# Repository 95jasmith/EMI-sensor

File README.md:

# EMI-sensor

This folder is for EMI conductivity meter being developed by Jonah Smith at Kansas State University for Dr. Stacey Kulesza in the Civil 
Engineering department.
All files are for the prototype and have only had limited testing.

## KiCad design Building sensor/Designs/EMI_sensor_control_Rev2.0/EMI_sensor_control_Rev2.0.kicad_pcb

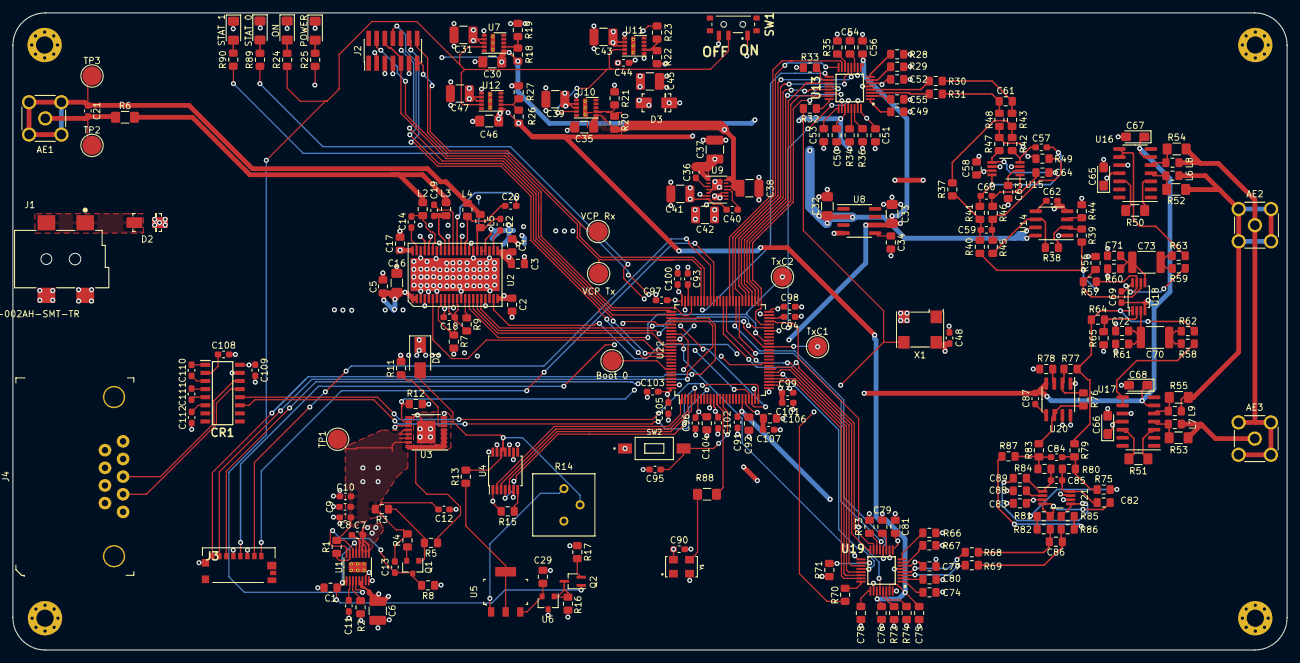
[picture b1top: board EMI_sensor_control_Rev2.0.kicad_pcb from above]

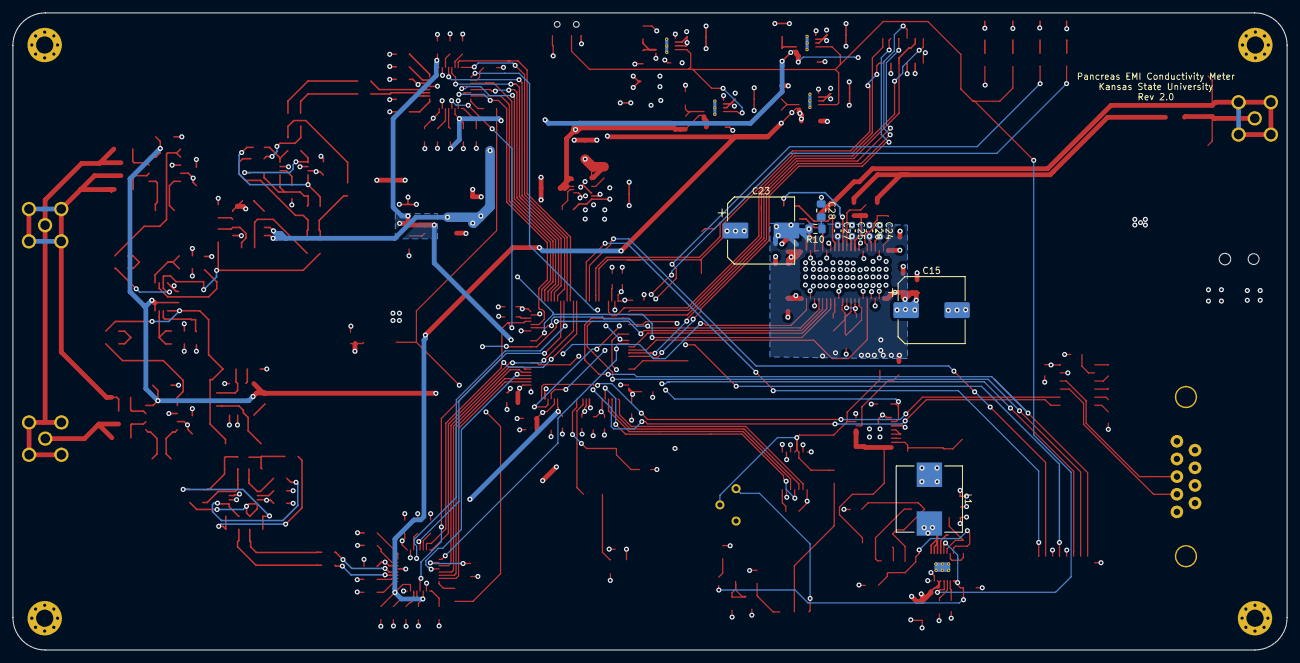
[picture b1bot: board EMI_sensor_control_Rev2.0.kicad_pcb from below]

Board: 4 copper layers, 200.0 x 100.0 mm, 266 parts (9 on the bottom side), 197 nets.

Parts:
AE1: Antenna_Loop Tx; SMA_Molex_73251-2200_Horizontal
AE2: Antenna_Loop Bx; SMA_Molex_73251-2200_Horizontal
AE3: Antenna_Loop Rx; SMA_Molex_73251-2200_Horizontal
Boot 0: TestPoint; TestPoint_Pad_D3.0mm
C1, C2, C3, C4, C5, C17, C29, C34, C49, C50, C51, C52, C53, C54, C55, C56, C58, C63, C74, C75, C76, C77, C78, C79, C80, C81, C83, C88, C92, C106: C 1u; C_0805_2012Metric_Pad1.15x1.40mm_HandSolder
C6, C31, C37, C38, C39, C41, C42, C43, C45, C47: C 10u; C_1210_3225Metric_Pad1.42x2.65mm_HandSolder
C7, C8, C9, C10, C11, C12, C14, C18, C19, C20, C22, C24, C25, C26, C27, C36, C40, C44, C48, C69, C90, C91, C95, C96, C97, C98, C99, C100, C101, C102, C103, C105, C107, C108, C109, C110, C111, C112: C 100n; C_0603_1608Metric_Pad1.05x0.95mm_HandSolder
C13, C60, C85: C 1n; C_0603_1608Metric_Pad1.05x0.95mm_HandSolder
C15: C 330u; CP_Elec_10x10
C16, C46: C 47u; C_1206_3216Metric_Pad1.42x1.75mm_HandSolder
C21: C 2700p; C_0603_1608Metric_Pad1.05x0.95mm_HandSolder
C23: C 470u; CP_Elec_10x10
C28: C 10n; C_0805_2012Metric_Pad1.15x1.40mm_HandSolder
C30: C 33u; C_1206_3216Metric_Pad1.42x1.75mm_HandSolder
C32: C 1u; C_1206_3216Metric_Pad1.42x1.75mm_HandSolder
C33, C35: C 22u; C_1206_3216Metric_Pad1.42x1.75mm_HandSolder
C57: C 270p; C_0603_1608Metric_Pad1.05x0.95mm_HandSolder
C59, C84: C 470p; C_0603_1608Metric_Pad1.05x0.95mm_HandSolder
C61, C86: C 22n; C_0805_2012Metric_Pad1.15x1.40mm_HandSolder
C62, C87: C 10p; C_0603_1608Metric_Pad1.05x0.95mm_HandSolder
C64, C82, C89: C 270p; C_0805_2012Metric_Pad1.15x1.40mm_HandSolder
C65, C66, C67, C68: C 100n; CP_EIA-3216-18_Kemet-A_Pad1.58x1.35mm_HandSolder
C70, C73: C 100n; C_1812_4532Metric_Pad1.30x3.40mm_HandSolder
C71, C72: C .047u; C_0805_2012Metric_Pad1.15x1.40mm_HandSolder
C93, C94: C 2.2u; C_0603_1608Metric_Pad1.05x0.95mm_HandSolder
C104: C 4.7u; C_0805_2012Metric_Pad1.15x1.40mm_HandSolder
CR1: ST3232BDR; SOIC127P600X175-16N
D1: B140-E3; D_SMA
D2, D3: B340A-13-F; DO-214AC
H1, H2, H3, H4: MountingHole_Pad; MountingHole_2.7mm_M2.5_Pad_Via
J1: PJ-002AH-SMT-TR; CUI_PJ-002AH-SMT-TR
J2: Conn_02x07_Odd_Even; PinHeader_2x07_P1.27mm_Vertical_SMD
J3: Micro_SD_Card; 47571-0001
J4: DB9_Female; DSUB-9_Receptical_A-DF_09_A_KG-T2S
L1: L 5.5u; L_Wuerth_HCI-1050
L2, L3, L4, L5: L 51n; L_0805_2012Metric_Pad1.15x1.40mm_HandSolder
L6, L7, L8, L9: L 1.2u; L_0805_2012Metric_Pad1.15x1.40mm_HandSolder
ON: LED On; LED_1206_3216Metric_Pad1.42x1.75mm_HandSolder
POWER: LED Power; LED_1206_3216Metric_Pad1.42x1.75mm_HandSolder
Q1: MMBT3906; SOT-23
Q2: CMST3904_TR_CMST3904_TR; SOT-323_SC-70_Handsoldering
R1, R16: R 5.1k; R_0805_2012Metric_Pad1.15x1.40mm_HandSolder
R2, R67: R 60.4k; R_0805_2012Metric_Pad1.15x1.40mm_HandSolder
R3, R5, R33, R34, R35, R36, R71, R72, R73, R74: R 100k; R_0805_2012Metric_Pad1.15x1.40mm_HandSolder
R4, R30, R31, R68, R69: R 1k; R_0805_2012Metric_Pad1.15x1.40mm_HandSolder
R6: R 590; R_1206_3216Metric_Pad1.42x1.75mm_HandSolder
R7: R 1; R_0805_2012Metric_Pad1.15x1.40mm_HandSolder
R8: R 4.99k; R_0805_2012Metric_Pad1.15x1.40mm_HandSolder
R9: R 150k; R_0805_2012Metric_Pad1.15x1.40mm_HandSolder
R10: R 3.3; R_0805_2012Metric_Pad1.15x1.40mm_HandSolder
R11: R 3.3k; R_0805_2012Metric_Pad1.15x1.40mm_HandSolder
R12, R15, R24, R25, R28, R29, R66: R 10k; R_0805_2012Metric_Pad1.15x1.40mm_HandSolder
R13: R 200; R_0805_2012Metric_Pad1.15x1.40mm_HandSolder
R14: 3386P-1-503LF; Potentiometer_Bourns_3386P_Vertical
R17: R 2.7k; R_0805_2012Metric_Pad1.15x1.40mm_HandSolder
R18: R 120k; R_0805_2012Metric_Pad1.15x1.40mm_HandSolder
R19: R 52.3k; R_0805_2012Metric_Pad1.15x1.40mm_HandSolder
R20, R22: R 102k; R_0805_2012Metric_Pad1.15x1.40mm_HandSolder
R21, R23, R27: R 25.5k; R_0805_2012Metric_Pad1.15x1.40mm_HandSolder
R26: R 51k; R_0805_2012Metric_Pad1.15x1.40mm_HandSolder
R32, R70: R 200 1%; R_0805_2012Metric_Pad1.15x1.40mm_HandSolder
R37, R49, R87: R 1.2K 1%; R_0805_2012Metric_Pad1.15x1.40mm_HandSolder
R38, R39, R76, R77: R 2k 1%; R_0805_2012Metric_Pad1.15x1.40mm_HandSolder
R40, R45, R79, R83: R 1.2k 1%; R_0805_2012Metric_Pad1.15x1.40mm_HandSolder
R41, R46, R80, R84: R 330 1%; R_0805_2012Metric_Pad1.15x1.40mm_HandSolder
R42, R47, R81, R85: R 4.99 1%; R_0805_2012Metric_Pad1.15x1.40mm_HandSolder
R43, R48, R82, R86: R 10 1%; R_0805_2012Metric_Pad1.15x1.40mm_HandSolder
R44, R78: R 1k 1%; R_0805_2012Metric_Pad1.15x1.40mm_HandSolder
R50, R51: R 22 1%; R_1206_3216Metric_Pad1.42x1.75mm_HandSolder
R52, R53, R54, R55: R 47 1%; R_1206_3216Metric_Pad1.42x1.75mm_HandSolder
R56, R65, R89, R90: R 1.2k; R_0805_2012Metric_Pad1.15x1.40mm_HandSolder
R57, R64: R 5.36k; R_0805_2012Metric_Pad1.15x1.40mm_HandSolder
R58, R63: R 1.6k; R_0805_2012Metric_Pad1.15x1.40mm_HandSolder
R59, R62: R 536; R_0805_2012Metric_Pad1.15x1.40mm_HandSolder
R60, R61: R 3.16k; R_0805_2012Metric_Pad1.15x1.40mm_HandSolder
R75: R 1.2K; R_0805_2012Metric_Pad1.15x1.40mm_HandSolder
R88: R 100 1%; R_1206_3216Metric_Pad1.42x1.75mm_HandSolder
STAT 0: LED Stat 0; LED_1206_3216Metric_Pad1.42x1.75mm_HandSolder
STAT 1: LED Stat 1; LED_1206_3216Metric_Pad1.42x1.75mm_HandSolder
SW1: SW_SPDT; EG1215AA
SW2: SW_Push; SW_1437566-4
TP1, TP2, TP3: TestPoint; TestPoint_Pad_D3.0mm
TxC1, TxC2: TestPoint; TestPoint_Pad_D3.0mm
U1: LT8610; MSOP-16-1EP_3x4mm_P0.5mm_EP1.65x2.85mm_ThermalVias
U2: DRV8412DDWR; SOIC-44
U3: 2019-12-05_20-39-13_LT3081EFE-PBF; TSSOP-16-1EP_4.4x5mm_P0.65mm
U4: MCP41HV51-103E_ST; TSSOP-14_4.4x5mm_P0.65mm
U5: LT3092EST_PBF; TO-261-4
U6: SI2309CDS-T1-GE3; SOT-23
U7, U11, U12: LMZM23601; Texas_SIL0010A_MicroSiP-10-1EP_3.8x3mm_P0.6mm_EP0.7x2.9mm_T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
U8: REF5025ID; SOIC-8_3.9x4.9mm_P1.27mm
U9: LT3032-3.3; Linear_DE14MA
U10: LMZM23601V5; Texas_SIL0010A_MicroSiP-10-1EP_3.8x3mm_P0.6mm_EP0.7x2.9mm_T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
U13, U19: ADS127L01IPBSR; QFP50P700X700X120-32N
U14, U20: AD8021ARZ; SOIC-8_3.9x4.9mm_P1.27mm
U15, U21: THS4551IDGKR; VSSOP-8_3.0x3.0mm_P0.65mm
U16, U17: INA163UA_2K5; SOIC-14_3.9x8.7mm_P1.27mm
U18: ADA4096-2ARMZ; MSOP-8_3x3mm_P0.65mm
U22: STM32F746VGTx; LQFP-100_14x14mm_P0.5mm
VCP Rx: TestPoint; TestPoint_Pad_D3.0mm
VCP Tx: TestPoint; TestPoint_Pad_D3.0mm
X1: ASV-xxxMHz; Oscillator_SMD_Abracon_ASV-4Pin_7.0x5.1mm
Y1: ECS-3963-400-BN-TR; OSC_ECS-3963-400-BN-TR

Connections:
25MHz_CLK: R88.1, Y1.3
3081IN: C8.2, C9.2, C10.2, C12.2, C13.1, L1.1, R1.2, R3.2, R4.2, TP1.1, U1.14, U3.12, U3.13, U3.14, U3.15
+2V5: C33.1, C56.1, C81.1, C91.2, C92.2, U8.6, U13.9, U19.9, U22.20
+3.3VADC: C36.1, C37.1, C48.1, C58.2, C65.1, C66.1, C69.1, C83.2, C90.1, U9.1, U15.3, U15.7, U16.11, U17.11, U18.8, U20.7, U20.8, U21.3, U21.7, X1.4, Y1.4
+3V0: C46.2, C51.2, C52.2, C75.2, C76.2, R26.1, U12.6, U13.6, U13.32, U19.27, U19.31
+3V3: C30.2, C50.2, C77.2, C96.1, C97.1, C98.1, C99.1, C100.1, C101.1, C102.1, C103.1, C104.1, C105.1, C106.2, C107.2, C109.1, CR1.16, J2.3, J3.4, R15.2, R18.1, R34.2, R72.2, U4.1, U7.6, U13.27, U19.6, U22.6, U22.11, U22.21, U22.27, U22.50, U22.75, U22.100
+5V: C32.1, C35.2, C38.1, R20.1, U8.2, U9.12, U9.14, U10.6, U14.7, U14.8
+BATT: C2.2, C3.2, C4.2, C5.2, C6.1, C15.1, C16.1, C17.1, C31.1, C39.1, C43.1, C44.1, C47.1, D2.K, R16.1, R25.1, SW1.1, U1.5, U1.6, U2.1, U2.2, U2.22, U2.23, U2.44, U4.14, U6.3, U7.2, U7.3, U10.2, U10.3, U11.2, U11.3, U12.2, U12.3
-3V3: C40.1, C41.1, C67.1, C68.1, C69.2, C87.2, U9.7, U16.6, U17.6, U18.4, U20.4
-5V: C42.1, C44.2, C45.2, C62.2, D3.A, R23.2, U9.6, U9.9, U9.10, U11.1, U11.11, U14.4
-BxFiltered: R38.1, R45.1, U14.6
-RxFiltered: R76.1, R83.1, U20.6
ADC_CLK: R32.2, R70.2, X1.3
ADC_Reset: U13.28, U19.28, U22.47
AINN_Bx: C61.1, R31.2, R48.2
AINN_Rx: C86.1, R69.2, R86.2
AINP_Bx: C61.2, R30.2, R43.2
AINP_Rx: C86.2, R68.2, R82.2
BxCoilAmp: R63.2, U16.8, U16.9
BxFiltered: R39.2, R40.1, R57.1, R59.2, U18.7
Bx_CS: U13.23, U22.51
Bx_Clk: U13.22, U22.46
Bx_DRDY: U13.19, U22.52
Bx_FIL0: U13.13, U22.55
Bx_FIL1: U13.12, U22.56
Bx_High: AE2.1, AE3.2, L8.2, R54.2
Bx_MISO: U13.20, U22.53
Bx_MOSI: U13.21, U22.54
Bx_OSR0: U13.16, U22.59
Bx_OSR1: U13.15, U22.60
Bx_START: U13.17, U22.85
DO_Rx: CR1.12, U22.25
DO_Tx: CR1.11, U22.24
GND: C1.2, C2.1, C3.1, C4.1, C5.1, C6.2, C8.1, C9.1, C10.1, C11.2, C12.1, C15.2, C16.2, C17.2, C23.1, C24.1, C25.1, C26.1, C27.1, C28.1, C29.2, C30.1, C31.2, C32.2, C33.2, C34.2, C35.1, C37.2, C38.2, C39.2, C41.2, C42.2, C43.2, C45.1, C46.1, C47.2, C48.2, C49.2, C50.1, C51.1, C52.1, C53.1, C54.1, C55.1, C56.2, C58.1, C63.1, C65.2, C66.2, C67.2, C68.2, C71.1, C72.1, C74.2, C75.1, C76.1, C77.1, C78.1, C79.1, C80.1, C81.2, C83.1, C88.1, C90.2, C91.1, C92.1, C93.1, C94.1, C95.2, C96.2, C97.2, C98.2, C99.2, C100.2, C101.2, C102.2, C103.2, C104.2, C105.2, C106.1, C107.1, C108.2, C109.2, C112.1, CR1.15, D3.K, J1.2, J1.3, J2.5, J2.7, J2.11, J3.6, J3.9, J4.5, ON.1, POWER.1, R2.1, R7.2, R8.1, R12.2, R17.1, R19.2, R21.2, R22.1, R27.2, R28.1, R29.1, R33.1, R35.2, R36.2, R44.1, R56.2, R60.2, R61.2, R65.2, R66.1, R67.1, R71.1, R73.2, R74.2, R78.1, STAT 0.1, STAT 1.1, SW1.3, SW2.1, U1.7, U1.8, U1.17, U2.3, U2.4, U2.5, U2.7, U2.13, U2.19, U2.20, U2.25, U2.29, U2.30, U2.37, U2.38, U2.42, U2.EPAD, U4.6, U4.8, U4.9, U4.10, U4.13, U7.1, U7.11, U8.4, U9.4, U9.5, U10.1, U10.11, U11.6, U12.1, U12.11, U13.5, U13.10, U13.26, U13.31, U14.1, U15.6, U16.10, U17.10, U19.5, U19.10, U19.26, U19.32, U20.1, U21.6, U22.10, U22.26, U22.49, U22.74, U22.99, X1.2, Y1.2
IMon: R12.1, U3.10, U22.34
INTVcc: C1.1, Q2.1, U1.1, U1.13
JTCK: J2.6, J2.9, U22.76
JTDI: J2.10, U22.77
JTDO: J2.8, U22.89
JTMS: J2.4, U22.72
JTRST: J2.12, U22.90
unnamed: AE1.1, C21.2, R6.1, TP2.1
unnamed: AE1.2, C21.1, L4.1, L5.1, TP3.1
unnamed: C7.1, L1.2, U1.9, U1.10, U1.11
unnamed: C7.2, U1.12
unnamed: C11.1, U1.2
unnamed: C13.2, Q1.3, R8.2, U1.16
unnamed: C14.1, L2.2, U2.39
unnamed: C14.2, U2.43
unnamed: C18.1, R7.1, R9.2, U2.8, U2.10, U2.12
unnamed: C18.2, U2.9, U2.11
unnamed: C19.1, L3.2, U2.36
unnamed: C19.2, U2.34
unnamed: C20.1, L4.2, U2.31
unnamed: C20.2, U2.33
unnamed: C22.1, L5.2, U2.28
unnamed: C22.2, U2.24
unnamed: C28.2, R10.1
unnamed: C29.1, U5.3, U6.2
unnamed: C34.1, U8.5
unnamed: C36.2, U9.3
unnamed: C40.2, U9.11
unnamed: C49.1, U13.1
unnamed: C53.2, U13.25
unnamed: C54.2, U13.11
unnamed: C55.2, U13.2
unnamed: C57.1, R42.1, U15.4
unnamed: C57.2, C60.2, R41.2, U15.8
unnamed: C59.1, R45.2, R46.1, R49.2
unnamed: C59.2, R37.1, R40.2, R41.1
unnamed: C60.1, C64.1, R46.2, U15.1
unnamed: C62.1, U14.5
unnamed: C63.2, U15.2
unnamed: C64.2, R47.1, U15.5
unnamed: C70.1, C72.2, R61.1, U18.3
unnamed: C70.2, R58.1, R62.1
unnamed: C71.2, C73.2, R60.1, U18.5
unnamed: C73.1, R59.1, R63.1
unnamed: C74.1, U19.1
unnamed: C78.2, U19.25
unnamed: C79.2, U19.11
unnamed: C80.2, U19.2
unnamed: C82.1, R81.1, U21.4
unnamed: C82.2, C85.2, R80.2, U21.8
unnamed: C84.1, R83.2, R84.1, R87.2
unnamed: C84.2, R75.1, R79.2, R80.1
unnamed: C85.1, C89.1, R84.2, U21.1
unnamed: C87.1, U20.5
unnamed: C88.2, U21.2
unnamed: C89.2, R85.1, U21.5
unnamed: C93.2, U22.73
unnamed: C94.2, U22.48
unnamed: C95.1, SW2.2, U22.14
unnamed: C108.1, CR1.2
unnamed: C110.1, CR1.3
unnamed: C110.2, CR1.1
unnamed: C111.1, CR1.5
unnamed: C111.2, CR1.4
unnamed: C112.2, CR1.6
unnamed: CR1.13, J4.2
unnamed: CR1.14, J4.3
unnamed: D1.2, R13.2, R14.2, U3.7, U4.11, U4.12
unnamed: D2.A, J1.1A, J1.1B
unnamed: ON.2, R24.2
unnamed: POWER.2, R25.2
unnamed: R89.2, STAT 0.2
unnamed: R90.2, STAT 1.2
unnamed: L2.1, L3.1, R6.2
unnamed: L6.2, R52.1, U16.4
unnamed: L7.2, R53.1, U17.4
unnamed: L8.1, R54.1, U16.5
unnamed: L9.1, R55.1, U17.5
unnamed: Q1.1, R3.1, R5.2
unnamed: Q1.2, R4.1
unnamed: Q2.2, R17.2
unnamed: Q2.3, R16.2, U6.1
unnamed: R1.1, U1.15
unnamed: R2.2, U1.3
unnamed: R9.1, U2.14
unnamed: R11.1, U3.6
unnamed: R13.1, U5.2, U5.4
unnamed: R14.3, U5.1
unnamed: R15.1, U4.7
unnamed: R18.2, R19.1, U7.7
unnamed: R20.2, R21.1, U10.7
unnamed: R22.2, R23.1, U11.7
unnamed: R26.2, R27.1, U12.7
unnamed: R28.2, U13.8
unnamed: R29.2, U13.7
unnamed: R30.1, U13.4
unnamed: R31.1, U13.3
unnamed: R32.1, U13.24
unnamed: R33.2, U13.18
unnamed: R34.1, U13.29
unnamed: R35.1, U13.14
unnamed: R36.1, U13.30
unnamed: R37.2, R42.2, R43.1
unnamed: R38.2, R39.1, U14.2
unnamed: R44.2, U14.3
unnamed: R47.2, R48.1, R49.1
unnamed: R50.1, U16.12
unnamed: R50.2, U16.3
unnamed: R51.1, U17.12
unnamed: R51.2, U17.3
unnamed: R56.1, R57.2, U18.6
unnamed: R64.2, R65.1, U18.2
unnamed: R66.2, U19.8
unnamed: R67.2, U19.7
unnamed: R68.1, U19.4
unnamed: R69.1, U19.3
unnamed: R70.1, U19.24
unnamed: R71.2, U19.18
unnamed: R72.1, U19.29
unnamed: R73.1, U19.14
unnamed: R74.1, U19.30
unnamed: R75.2, R81.2, R82.1
unnamed: R76.2, R77.1, U20.2
unnamed: R78.2, U20.3
unnamed: R85.2, R86.1, R87.1
unnamed: R88.2, U22.12
unnamed: R89.1, U22.22
unnamed: R90.1, U22.23
unnamed: Boot 0.1, U22.94
Pwr1: R24.1, SW1.2, U1.4, U7.4, U10.4, U11.4, U12.4
RSET_AB: U2.16, U22.87
RSET_CD: U2.6, U22.88
RxCoilAmp: R58.2, U17.8, U17.9
RxFiltered: R62.2, R64.1, R77.2, R79.1, U18.1
Rx_CS: U19.23, U22.28
Rx_Clk: U19.22, U22.29
Rx_DRDY: U19.19, U22.32
Rx_FIL0: U19.13, U22.57
Rx_FIL1: U19.12, U22.58
Rx_High: AE3.1, L7.1, R53.2
Rx_Low: AE2.2, L6.1, L9.2, R52.2, R55.2
Rx_MISO: U19.20, U22.30
Rx_MOSI: U19.21, U22.31
Rx_OSR0: U19.16, U22.61
Rx_OSR1: U19.15, U22.62
Rx_START: U19.17, U22.86
SD_CK: J3.5, U22.80
SD_CMD: J3.3, U22.83
SD_D0: J3.7, U22.66
SD_D1: J3.8, U22.65
SD_D2: J3.1, U22.78
SD_D3: J3.2, U22.79
TxC1: TxC1.1, U2.17, U22.39
TxC2: TxC2.1, U2.15, U22.41
Tx_CLK: U4.2, U22.1
Tx_CS: U4.3, U22.3
Tx_Fault: U2.18, U22.45
Tx_MISO: U4.5, U22.4
Tx_MOSI: U4.4, U22.5
Tx_OTW: U2.21, U22.44
VCP_Rx: J2.13, U22.68, VCP Rx.1
VCP_Tx: J2.14, U22.69, VCP Tx.1
Vvar: C23.2, C24.2, C25.2, C26.2, C27.2, D1.1, R5.1, R10.2, R11.2, U2.26, U2.27, U2.32, U2.35, U2.40, U2.41, U3.1, U3.2, U3.3, U3.4, U3.5, U3.8, U3.9, U3.11, U3.16, U3.17

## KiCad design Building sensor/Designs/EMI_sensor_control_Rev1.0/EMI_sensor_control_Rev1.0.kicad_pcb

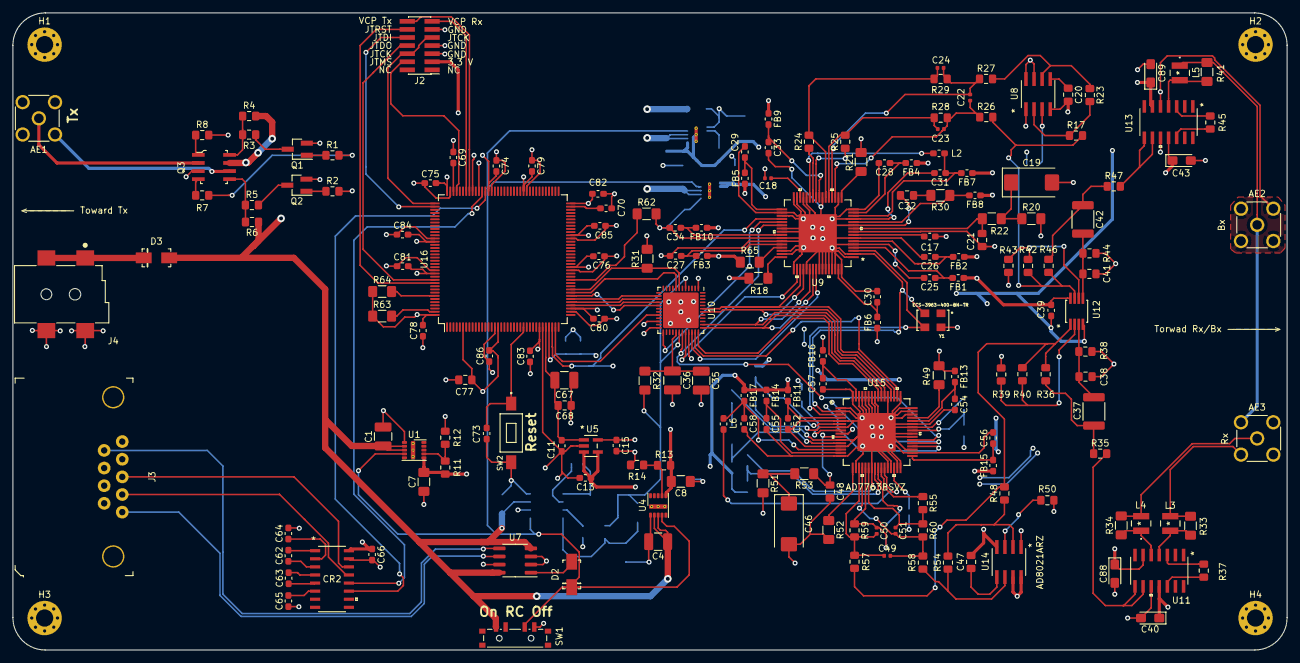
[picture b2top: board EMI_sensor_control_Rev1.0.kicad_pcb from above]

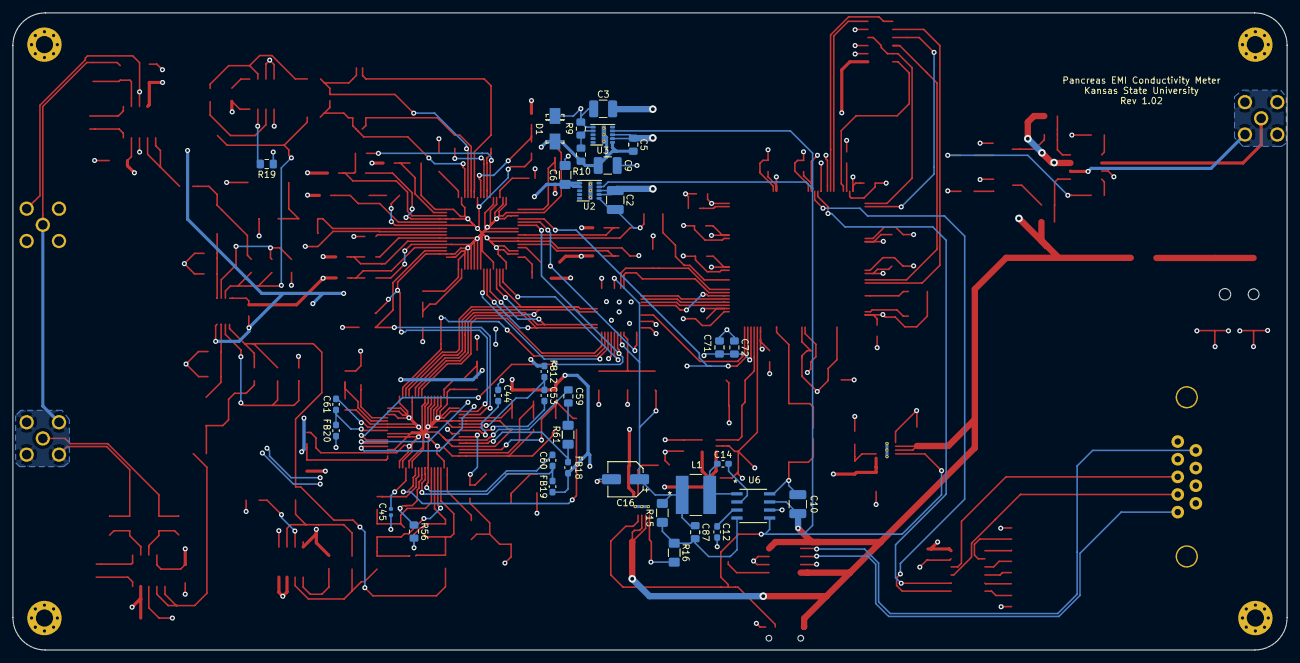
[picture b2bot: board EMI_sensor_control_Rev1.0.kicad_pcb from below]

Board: 4 copper layers, 200.0 x 100.0 mm, 216 parts (34 on the bottom side), 152 nets.

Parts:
AE1: Antenna_Loop Tx; SMA_Molex_73251-2200_Horizontal
AE2: Antenna_Loop Bx; SMA_Molex_73251-2200_Horizontal
AE3: Antenna_Loop Rx; SMA_Molex_73251-2200_Horizontal
C1, C2, C3, C4, C9, C10, C35, C36, C67: C 10u; C_1210_3225Metric_Pad1.42x2.65mm_HandSolder
C5: C 100n; C_0805_2012Metric_Pad1.15x1.40mm_HandSolder
C6: C 22u; C_1206_3216Metric_Pad1.42x1.75mm_HandSolder
C7: C 33u; C_1206_3216Metric_Pad1.42x1.75mm_HandSolder
C8: C 68u; C_1206_3216Metric_Pad1.42x1.75mm_HandSolder
C11, C13, C14, C15, C17, C25, C26, C27, C28, C29, C30, C31, C33, C34, C39, C44, C52, C53, C54, C55, C56, C57, C58, C60, C61, C62, C63, C64, C65, C66, C73, C74, C75, C76, C78, C79, C80, C81, C82, C83, C84, C85, C86: C 100n; C_0603_1608Metric_Pad1.05x0.95mm_HandSolder
C12, C69, C70: C 2.2u; C_0603_1608Metric_Pad1.05x0.95mm_HandSolder
C16: C 330u; CP_Elec_5x5.3
C18, C23, C24, C45, C50, C51: C 33p; C_0402_1005Metric
C19, C46: C 100u; CP_EIA-7343-30_AVX-N_Pad2.25x2.55mm_HandSolder
C20, C47: C 10p; C_0805_2012Metric_Pad1.15x1.40mm_HandSolder
C21, C32, C48, C59, C71: C 10n; C_0805_2012Metric_Pad1.15x1.40mm_HandSolder
C22, C49: C 5.6p; C_0402_1005Metric
C37, C42: C 100n; C_1812_4532Metric_Pad1.30x3.40mm_HandSolder
C38, C41: C .047u; C_0805_2012Metric_Pad1.15x1.40mm_HandSolder
C40, C43, C88, C89: C 100n; CP_EIA-3216-18_Kemet-A_Pad1.58x1.35mm_HandSolder
C68, C72: C 1u; C_0805_2012Metric_Pad1.15x1.40mm_HandSolder
C77: C 4.7u; C_0805_2012Metric_Pad1.15x1.40mm_HandSolder
C87: C 1.8n; C_0805_2012Metric_Pad1.15x1.40mm_HandSolder
CR2: ST3232BDR
D1, D2, D3: B340A-13-F; DO-214AC
FB1, FB2, FB3, FB4, FB5, FB6, FB7, FB8, FB9, FB10, FB11, FB12, FB13, FB14, FB15, FB16, FB17, FB18, FB19, FB20: Ferrite_Bead; C_0603_1608Metric_Pad1.05x0.95mm_HandSolder
H1, H2, H3, H4: MountingHole_Pad; MountingHole_2.7mm_M2.5_Pad_Via
J2: Conn_02x07_Odd_Even; PinHeader_2x07_P1.27mm_Vertical_SMD
J3: DB9_Female; DSUB-9_Receptical_A-DF_09_A_KG-T2S
J4: PJ-002AH-SMT-TR; CUI_PJ-002AH-SMT-TR
L1: L 6.8u; SRN6045-6R8Y
L2, L6: L 8.2n; L_0603_1608Metric_Pad1.05x0.95mm_HandSolder
L3, L4, L5: L 1.2u; AISC-1008-1R2G-T
Q1, Q2: BSR14; SOT-23_Handsoldering
Q3: DMHC3025LSD-13; SOIC-8_W3.9mm
R1, R2, R3, R5, R7, R8, R19, R26, R27, R50, R57, R58: R 1k; R_0805_2012Metric_Pad1.15x1.40mm_HandSolder
R4, R6: R 4.7k; R_0805_2012Metric_Pad1.15x1.40mm_HandSolder
R9: R 102k; R_0805_2012Metric_Pad1.15x1.40mm_HandSolder
R10, R14: R 25.5k; R_0805_2012Metric_Pad1.15x1.40mm_HandSolder
R11: R 120k; R_0805_2012Metric_Pad1.15x1.40mm_HandSolder
R12: R 52.3k; R_0805_2012Metric_Pad1.15x1.40mm_HandSolder
R13: R 38.3k; R_0805_2012Metric_Pad1.15x1.40mm_HandSolder
R15: R 4.42k; R_1206_3216Metric_Pad1.42x1.75mm_HandSolder
R16: R 22.1k; R_1206_3216Metric_Pad1.42x1.75mm_HandSolder
R17, R23, R48, R54: R 2k; R_0805_2012Metric_Pad1.15x1.40mm_HandSolder
R18, R49, R62, R63, R64, R65: R 10k; R_1206_3216Metric_Pad1.42x1.75mm_HandSolder
R20, R32, R51: R 100; R_1206_3216Metric_Pad1.42x1.75mm_HandSolder
R21, R52: R 160k; R_1206_3216Metric_Pad1.42x1.75mm_HandSolder
R22, R30, R53, R61: R 10; R_1206_3216Metric_Pad1.42x1.75mm_HandSolder
R24, R25, R55, R56: R 18; R_0805_2012Metric_Pad1.15x1.40mm_HandSolder
R28, R29, R59, R60: R 649; R_0805_2012Metric_Pad1.15x1.40mm_HandSolder
R31: R 1M; R_1206_3216Metric_Pad1.42x1.75mm_HandSolder
R33, R34, R41: R 47; R_1206_3216Metric_Pad1.42x1.75mm_HandSolder
R35, R47: R 1.6k; R_0805_2012Metric_Pad1.15x1.40mm_HandSolder
R36, R46: R 536; R_0805_2012Metric_Pad1.15x1.40mm_HandSolder
R37, R45: R 22ohm; R_0805_2012Metric_Pad1.15x1.40mm_HandSolder
R38, R44: R 3.16k; R_0805_2012Metric_Pad1.15x1.40mm_HandSolder
R39, R43: R 1.2k; R_0805_2012Metric_Pad1.15x1.40mm_HandSolder
R40, R42: R 5.36k; R_0805_2012Metric_Pad1.15x1.40mm_HandSolder
SW1: SW_SP3T; SW_SP3T_PCM13
SW2: SW_Push; SW_1437566-4
U1, U3, U4: LMZM23601; Texas_SIL0010A_MicroSiP-10-1EP_3.8x3mm_P0.6mm_EP0.7x2.9mm_T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
U2: LMZM23601V5; Texas_SIL0010A_MicroSiP-10-1EP_3.8x3mm_P0.6mm_EP0.7x2.9mm_T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
U5: REF2041AIDDCT
U6: LMR23610ADDAR
U7: ADG419BR; SOIC-8_3.9x4.9mm_P1.27mm
U8, U14: AD8021ARZ
U9, U15: AD7763BSVZ
U10: ICE40UP5K-SG48ITR; QFN-48-1EP_7x7mm_P0.5mm_EP5.6x5.6mm
U11, U13: INA163UA_2K5; INA163UA&slash_2K5
U12: ADA4096-2ARMZ
U16: STM32F412ZETx; LQFP-144_20x20mm_P0.5mm
Y1: ECS-3963-400-BN-TR; OSC_ECS-3963-400-BN-TR

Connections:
5vComm: J3.9, U7.5
+1V2: C16.1, C87.1, L1.1, R15.1, R32.1, U10.5, U10.30
+2V5: C8.2, FB2.1, FB3.1, FB5.1, FB6.1, FB10.1, FB12.1, FB13.1, FB15.1, FB16.1, FB20.1, R13.1, R18.1, R49.1, R65.1, U4.6, U10.24, U10.33
+5V: C6.2, C13.1, C39.1, C40.1, C43.1, FB1.1, FB4.1, FB7.1, FB8.1, FB9.1, FB11.1, FB14.1, FB17.1, FB18.1, FB19.1, U2.6, U2.7, U5.3, U5.4, U8.7, U8.8, U11.11, U12.8, U13.11, U14.7, U14.8, Y1.4
+BATT: C1.1, C2.1, C3.1, C4.1, C5.1, C10.1, D3.A, Q3.7, R4.1, R6.1, SW1.1, U1.2, U1.3, U2.2, U2.3, U3.2, U3.3, U4.2, U4.3, U6.7, U7.4, U7.8
-5V: C5.2, C9.2, C20.2, C39.2, C47.2, C88.1, C89.1, D1.A, R10.2, U3.1, U3.11, U8.4, U11.6, U12.4, U13.6, U14.4
ADCReset: U9.37, U10.25, U15.37
ADCSync: U9.36, U15.36, U16.34
ADR0b: R18.2, U9.48
ADR0r: AE2.2, C1.2, C2.2, C3.2, C4.2, C6.1, C7.1, C8.1, C9.1, C10.2, C11.2, C12.2, C13.2, C15.2, C16.2, C17.2, C18.2, C19.2, C21.2, C25.2, C26.2, C27.2, C28.2, C29.2, C30.2, C31.2, C32.2, C33.2, C34.2, C35.2, C36.2, C38.1, C40.2, C41.1, C43.2, C44.2, C45.2, C46.2, C48.2, C52.2, C53.2, C54.2, C55.2, C56.2, C57.2, C58.2, C59.2, C60.2, C61.2, C64.2, C65.1, C66.2, C67.1, C68.1, C69.1, C70.1, C71.1, C72.1, C73.2, C74.1, C75.1, C76.1, C77.1, C78.1, C79.1, C80.1, C81.1, C82.1, C83.1, C84.1, C85.1, C86.1, C88.2, C89.2, CR2.15, D1.K, H1.1, H2.1, H3.1, H4.1, J2.5, J2.7, J2.11, J3.5, J4.2, J4.3, Q1.2, Q2.2, Q3.3, R9.1, R12.2, R14.2, R16.2, R19.1, R21.2, R38.2, R39.2, R43.2, R44.2, R50.1, R52.2, R62.2, SW1.4, SW2.2, U1.1, U1.11, U2.1, U2.11, U3.6, U4.1, U4.11, U5.2, U6.6, U6.8, U7.2, U7.3, U7.7, U8.1, U9.1, U9.2, U9.5, U9.7, U9.9, U9.11, U9.13, U9.16, U9.18, U9.23, U9.28, U9.29, U9.31, U9.32, U9.34, U9.35, U9.39, U9.40, U9.42, U9.43, U9.46, U9.47, U9.49, U9.53, U9.57, U9.58, U9.59, U9.60, U9.61, U9.62, U9.64, U9.EP, U10.49, U11.10, U13.5, U13.10, U14.1, U15.1, U15.2, U15.5, U15.7, U15.9, U15.11, U15.13, U15.16, U15.18, U15.23, U15.28, U15.29, U15.31, U15.32, U15.34, U15.35, U15.39, U15.40, U15.42, U15.43, U15.46, U15.47, U15.48, U15.49, U15.53, U15.57, U15.58, U15.59, U15.60, U15.61, U15.62, U15.64, U15.EP, U16.16, U16.31, U16.38, U16.51, U16.61, U16.83, U16.94, U16.107, U16.120, U16.130, Y1.2
BxCoilAmp: R47.2, U13.8, U13.9
BxCoilsig: AE2.1, AE3.2, L3.1, L5.1, R33.2, R41.2
BxFiltered: R17.2, R26.2, R42.1, R46.2, U12.7
DO_Rx: CR2.12, U16.97
DO_Tx: CR2.11, U16.96
DRDY: U9.38, U10.31, U15.38
FPGA_CDONE: R31.1, U10.7, U16.45
FPGA_CLK: U10.15, U16.41
FPGA_Config: U10.8, U16.44
FPGA_MISO: U10.14, U16.42
FPGA_MOSI: U10.17, U16.43
FPGA_SS: U10.16, U16.40
FSI: U9.51, U10.43, U15.51
FSOb: U9.56, U10.34
FSOr: U10.36, U15.56
JTCK: J2.6, J2.9, U16.109
JTDI: J2.10, U16.110
JTDO: J2.8, U16.133
JTMS: J2.4, U16.105
JTRST: J2.12, U16.134
MCLK: U9.3, U15.3, Y1.3
unnamed: AE1.1, Q3.2
unnamed: AE1.2, Q3.6
unnamed: C12.1, U6.3
unnamed: C14.1, L1.2, U6.1
unnamed: C14.2, U6.2
unnamed: C17.1, U9.8
unnamed: C18.1, U9.30
unnamed: C19.1, R20.1, R22.2
unnamed: C20.1, U8.5
unnamed: C21.1, R22.1, U9.10
unnamed: C32.1, R30.2
unnamed: C35.1, C36.1, R32.2, U10.29
unnamed: C37.1, C38.2, R38.1, U12.3
unnamed: C37.2, R35.1, R36.1
unnamed: C41.2, C42.2, R44.1, U12.5
unnamed: C42.1, R46.1, R47.1
unnamed: C44.1, U15.8
unnamed: C45.1, U15.30
unnamed: C46.1, R51.1, R53.2
unnamed: C47.1, U14.5
unnamed: C48.1, R53.1, U15.10
unnamed: C59.1, R61.2
unnamed: C62.1, CR2.3
unnamed: C62.2, CR2.1
unnamed: C63.1, CR2.5
unnamed: C63.2, CR2.4
unnamed: C64.1, CR2.2
unnamed: C65.2, CR2.6
unnamed: C69.2, U16.106
unnamed: C70.2, U16.71
unnamed: C73.1, SW2.1, U16.25
unnamed: C87.2, R15.2, R16.1, U6.4
unnamed: CR2.13, J3.2
unnamed: CR2.14, J3.3
unnamed: D2.A, U7.1
unnamed: D3.K, J4.1A, J4.1B
unnamed: L3.2, R33.1, U11.4
unnamed: L4.1, R34.1, U11.5
unnamed: L5.2, R41.1, U13.4
unnamed: Q1.1, R1.1
unnamed: Q1.3, R3.2
unnamed: Q2.1, R2.1
unnamed: Q2.3, R5.2
unnamed: Q3.1, R8.1
unnamed: Q3.4, R7.1
unnamed: Q3.5, R5.1, R6.2
unnamed: Q3.8, R3.1, R4.2
unnamed: R9.2, R10.1, U3.7
unnamed: R11.2, R12.1, U1.7
unnamed: R13.2, R14.1, U4.7
unnamed: R17.1, R23.2, U8.2
unnamed: R19.2, U8.3
unnamed: R21.1, U9.17
unnamed: R23.1, R27.2, U8.6
unnamed: R24.1, U9.26
unnamed: R25.1, U9.25
unnamed: R37.1, U11.12
unnamed: R37.2, U11.3
unnamed: R39.1, R40.2, U12.2
unnamed: R42.2, R43.1, U12.6
unnamed: R45.1, U13.12
unnamed: R45.2, U13.3
unnamed: R48.1, R54.2, U14.2
unnamed: R50.2, U14.3
unnamed: R52.1, U15.17
unnamed: R54.1, R58.2, U14.6
unnamed: R55.1, U15.26
unnamed: R56.1, U15.25
unnamed: R62.1, U16.48
unnamed: R63.2, U16.143
unnamed: R64.2, U16.138
PWROn: J3.1, U7.6
Pin4b: C25.1, FB1.2, U9.4
Pin4r: C52.1, FB11.2, U15.4
Pin6b: C26.1, FB2.2, U9.6
Pin6r: C53.1, FB12.2, U15.6
Pin12b: FB8.2, R30.1, U9.12
Pin12r: FB18.2, R61.1, U15.12
Pin14b: C31.1, FB7.2, L2.2, U9.14
Pin14r: C58.1, FB17.2, L6.2, U15.14
Pin15b: C28.1, FB4.2, U9.15
Pin15r: C55.1, FB14.2, U15.15
Pin19b: C22.1, C23.2, R26.1, R28.2, U9.19
Pin19r: C49.1, C50.2, R57.1, R59.2, U15.19
Pin20b: C22.2, C24.2, R27.1, R29.2, U9.20
Pin20r: C49.2, C51.2, R58.1, R60.2, U15.20
Pin21b-: C23.1, R25.2, R28.1, U9.21
Pin21r-: C50.1, R56.2, R59.1, U15.21
Pin22b+: C24.1, R24.2, R29.1, U9.22
Pin22r+: C51.1, R55.2, R60.1, U15.22
Pin24b: C33.1, FB9.2, U9.24
Pin24r: C60.1, FB19.2, U15.24
Pin27b: L2.1, U9.27
Pin27r: L6.1, U15.27
Pin33b: C29.1, FB5.2, U9.33
Pin33r: C56.1, FB15.2, U15.33
Pin41b: C34.1, FB10.2, U9.41
Pin41r: C61.1, FB20.2, U15.41
Pin44b: C27.1, FB3.2, U9.44
Pin44r: C54.1, FB13.2, U15.44
Pin63b: C30.1, FB6.2, U9.63
Pin63r: C57.1, FB16.2, U15.63
Pwr1: D2.K, SW1.3, U1.4, U2.4, U3.4, U4.4, U6.5
RxCoilAmp: R35.2, U11.8, U11.9
RxCoilsig+: AE3.1, L4.2, R34.2
RxFiltered: R36.2, R40.1, R48.2, R57.2, U12.1
SCO: U9.55, U10.37, U15.55
SDI: U9.52, U10.42, U15.52
SDLb: U9.50, U10.32
SDLr: U10.35, U15.50
SDO: U9.54, U10.38, U15.54
SH0b: R65.2, U9.45
SH0r: R49.2, U15.45
TX_On: U10.20, U16.35
TxC1: R1.2, R7.2, U16.100
TxC2: R2.2, R8.2, U16.98
VCP_Rx: J2.13, U16.102
VCP_Tx: J2.14, U16.101
VDD1: C7.2, C66.1, C71.2, C72.2, C74.2, C75.2, C76.2, C77.2, C78.2, C79.2, C80.2, C81.2, C82.2, C83.2, C84.2, C85.2, C86.2, CR2.16, J2.3, R11.1, R31.2, R63.1, R64.1, U1.6, U10.1, U10.22, U16.6, U16.17, U16.30, U16.33, U16.39, U16.52, U16.62, U16.72, U16.84, U16.95, U16.108, U16.121, U16.131, U16.144
Vref2.1: C11.1, C67.2, C68.2, U5.1, U16.32
Vref4.1: C15.1, R20.2, R51.2, U5.5

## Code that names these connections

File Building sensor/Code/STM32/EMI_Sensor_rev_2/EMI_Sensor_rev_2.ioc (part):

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Mcu.Name=STM32F746VGTx
Mcu.Package=LQFP100
Mcu.UserName=STM32F746VGTx
PA0/WKUP.GPIOParameters=GPIO_Label
PA0/WKUP.GPIO_Label=STAT_LED_0
PA0/WKUP.Signal=GPIO_Output
PA1.GPIOParameters=GPIO_Label
PA1.GPIO_Label=STAT_LED_1
PA1.Signal=GPIO_Output
PA10.GPIOParameters=GPIO_Label
PA10.GPIO_Label=VCP_Rx
PA10.Mode=Asynchronous
PA10.Signal=USART1_RX
PA13.Mode=JTAG_5_pins
PA13.Signal=SYS_JTMS-SWDIO
PA14.Mode=JTAG_5_pins
PA14.Signal=SYS_JTCK-SWCLK
PA15.Mode=JTAG_5_pins
PA15.Signal=SYS_JTDI
PA2.GPIOParameters=GPIO_Label
PA2.GPIO_Label=USART_DO_Tx
PA2.Mode=Asynchronous
PA2.Signal=USART2_TX
PA3.GPIOParameters=GPIO_Label
PA3.GPIO_Label=USART_DO_Rx
PA3.Mode=Asynchronous
PA3.Signal=USART2_RX
PA4.Mode=NSS_Signal_Hard_Output
PA4.Signal=SPI1_NSS
PA5.Mode=Full_Duplex_Master
PA5.Signal=SPI1_SCK
PA6.Mode=Full_Duplex_Master
PA6.Signal=SPI1_MISO
PA7.Mode=Full_Duplex_Master
PA7.Signal=SPI1_MOSI
PA9.GPIOParameters=GPIO_Label
PA9.GPIO_Label=VCP_Tx
PA9.Mode=Asynchronous
PA9.Signal=USART1_TX
PB0.GPIOParameters=GPIO_Label
PB0.GPIO_Label=I_Mon
PB0.Signal=ADCx_IN8
PB10.GPIOParameters=GPIO_Label
PB10.GPIO_Label=Bx_CLK
PB10.Mode=Full_Duplex_Master
PB10.Signal=SPI2_SCK
PB11.GPIOParameters=GPIO_Label
PB11.GPIO_Label=ADC_Sync
PB11.Signal=GPIO_Output
PB12.GPIOParameters=GPIO_Label
PB12.GPIO_Label=Bx_CS
PB12.Mode=NSS_Signal_Hard_Output
PB12.Signal=SPI2_NSS
PB13.GPIOParameters=GPIO_Label
PB13.GPIO_Label=Bx_DRDY
PB13.Signal=GPIO_Input
PB14.GPIOParameters=GPIO_Label
PB14.GPIO_Label=Bx_MISO
PB14.Mode=Full_Duplex_Master
PB14.Signal=SPI2_MISO
PB15.GPIOParameters=GPIO_Label
PB15.GPIO_Label=Bx_MOSI
PB15.Mode=Full_Duplex_Master
PB15.Signal=SPI2_MOSI
PB3.Mode=JTAG_5_pins
PB3.Signal=SYS_JTDO-SWO
PB4.Mode=JTAG_5_pins
PB4.Signal=SYS_JTRST
PC10.Mode=SD_4_bits_Wide_bus
PC10.Signal=SDMMC1_D2
PC11.Mode=SD_4_bits_Wide_bus
PC11.Signal=SDMMC1_D3
PC12.Mode=SD_4_bits_Wide_bus
PC12.Signal=SDMMC1_CK
PC14/OSC32_IN.GPIOParameters=GPIO_Label
PC14/OSC32_IN.GPIO_Label=Tx_OTW
PC14/OSC32_IN.Signal=GPXTI14
PC15/OSC32_OUT.GPIOParameters=GPIO_Label
PC15/OSC32_OUT.GPIO_Label=Tx_Fault
PC15/OSC32_OUT.Signal=GPXTI15
PC4.GPIOParameters=GPIO_Label
PC4.GPIO_Label=Rx_DRDY
PC4.Signal=GPIO_Input
PC8.Mode=SD_4_bits_Wide_bus
PC8.Signal=SDMMC1_D0
PC9.Mode=SD_4_bits_Wide_bus
PC9.Signal=SDMMC1_D1
PD10.GPIOParameters=GPIO_Label
PD10.GPIO_Label=Rx_FIL0
PD10.Signal=GPIO_Output
PD11.GPIOParameters=GPIO_Label
PD11.GPIO_Label=Rx_FIL1
PD11.Signal=GPIO_Output
PD12.GPIOParameters=GPIO_Label
PD12.GPIO_Label=Bx_OSR0
PD12.Signal=GPIO_Output
PD13.GPIOParameters=GPIO_Label
PD13.GPIO_Label=Bx_OSR1
PD13.Signal=GPIO_Output
PD14.GPIOParameters=GPIO_Label
PD14.GPIO_Label=Rx_OSR0
PD14.Signal=GPIO_Output
PD15.GPIOParameters=GPIO_Label
PD15.GPIO_Label=Rx_OSR1
PD15.Signal=GPIO_Output
PD2.Mode=SD_4_bits_Wide_bus
PD2.Signal=SDMMC1_CMD
PD4.GPIOParameters=GPIO_Label
PD4.GPIO_Label=Bx_START
PD4.Signal=GPIO_Output
PD5.GPIOParameters=GPIO_Label
PD5.GPIO_Label=Rx_START
PD5.Signal=GPIO_Output
PD6.GPIOParameters=GPIO_Label
PD6.GPIO_Label=RSET_AD
PD6.Signal=GPIO_Output
PD7.GPIOParameters=GPIO_Label
PD7.GPIO_Label=RSET_CD
PD7.Signal=GPIO_Output
PD8.GPIOParameters=GPIO_Label
PD8.GPIO_Label=Bx_FIL0
PD8.Signal=GPIO_Output
PD9.GPIOParameters=GPIO_Label
PD9.GPIO_Label=Bx_FIL1
PD9.Signal=GPIO_Output
PE11.GPIOParameters=GPIO_Label
PE11.GPIO_Label=Tx_C2
PE11.Signal=S_TIM1_CH2
PE2.GPIOParameters=GPIO_Label
PE2.GPIO_Label=Tx_CLK
PE2.Mode=Full_Duplex_Master
PE2.Signal=SPI4_SCK
PE4.GPIOParameters=GPIO_Label
PE4.GPIO_Label=Tx_CS
PE4.Mode=NSS_Signal_Hard_Input
PE4.Signal=SPI4_NSS
PE5.GPIOParameters=GPIO_Label
PE5.GPIO_Label=Tx_MISO
PE5.Mode=Full_Duplex_Master
PE5.Signal=SPI4_MISO
PE6.GPIOParameters=GPIO_Label
PE6.GPIO_Label=Tx_MOSI
PE6.Mode=Full_Duplex_Master
PE6.Signal=SPI4_MOSI
PE9.GPIOParameters=GPIO_Label
PE9.GPIO_Label=Tx_C1
PE9.Signal=S_TIM1_CH1
PH0/OSC_IN.Mode=HSE-External-Clock-Source
PH0/OSC_IN.Signal=RCC_OSC_IN
PH1/OSC_OUT.Mode=HSE-External-Clock-Source
PH1/OSC_OUT.Signal=RCC_OSC_OUT
RCC.HSE_VALUE=25000000
RCC.SYSCLKFreq_VALUE=16000000
board=custom

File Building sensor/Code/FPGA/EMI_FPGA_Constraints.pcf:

# ##############################################################################

# iCEcube PCF

# Version:            2014.12.27052

# File Generated:     Apr 27 2015 09:46:33

# Family & Device:    iCE40UP5K

# Package:            SG48

# ##############################################################################

### Main FPGA Clock
set_io i_Clk 15

### General Input
set_io i_Tx_On 20
set_io o_ADC_Reset 25


### ADC Both
set_io DRDY 31
set_io SCO 37
set_io FSI 43
set_io SDO 38
set_io SDI 42

### ADC Rx
set_io SDLr 35
set_io FSOr 36

### ADC Bx
set_io SDLb 32
set_io FSOb 34

## SPI Outputs
set_io MISO 14
set_io MOSI 17
set_io SS 16

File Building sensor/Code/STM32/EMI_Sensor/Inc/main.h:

/* USER CODE BEGIN Header */
/**
  ******************************************************************************
  * @file           : main.h
  * @brief          : Header for main.c file.
  *                   This file contains the common defines of the application.
  ******************************************************************************
  * @attention
  *
  * <h2><center>&copy; Copyright (c) 2019 STMicroelectronics.
  * All rights reserved.</center></h2>
  *
  * This software component is licensed by ST under BSD 3-Clause license,
  * the "License"; You may not use this file except in compliance with the
  * License. You may obtain a copy of the License at:
  *                        opensource.org/licenses/BSD-3-Clause
  *
  ******************************************************************************
  */
/* USER CODE END Header */

/* Define to prevent recursive inclusion -------------------------------------*/
#ifndef __MAIN_H
#define __MAIN_H

#ifdef __cplusplus
extern "C" {
#endif

/* Includes ------------------------------------------------------------------*/
#include "stm32f4xx_hal.h"

/* Private includes ----------------------------------------------------------*/
/* USER CODE BEGIN Includes */

/* USER CODE END Includes */

/* Exported types ------------------------------------------------------------*/
/* USER CODE BEGIN ET */

/* USER CODE END ET */

/* Exported constants --------------------------------------------------------*/
/* USER CODE BEGIN EC */

/* USER CODE END EC */

/* Exported macro ------------------------------------------------------------*/
/* USER CODE BEGIN EM */

/* USER CODE END EM */

void HAL_TIM_MspPostInit(TIM_HandleTypeDef *htim);

/* Exported functions prototypes ---------------------------------------------*/
void Error_Handler(void);

/* USER CODE BEGIN EFP */

/* USER CODE END EFP */

/* Private defines -----------------------------------------------------------*/
#define TX_On_Pin GPIO_PIN_0
#define TX_On_GPIO_Port GPIOA
#define ADCSync_Pin GPIO_PIN_1
#define ADCSync_GPIO_Port GPIOA
#define FPGA_SS_Pin GPIO_PIN_4
#define FPGA_SS_GPIO_Port GPIOA
#define FPGA_CLK_Pin GPIO_PIN_5
#define FPGA_CLK_GPIO_Port GPIOA
#define FPGA_MISO_Pin GPIO_PIN_6
#define FPGA_MISO_GPIO_Port GPIOA
#define FPGA_MOSI_Pin GPIO_PIN_7
#define FPGA_MOSI_GPIO_Port GPIOA
#define FPGA_Config_Pin GPIO_PIN_4
#define FPGA_Config_GPIO_Port GPIOC
#define FPGA_CDone_Pin GPIO_PIN_5
#define FPGA_CDone_GPIO_Port GPIOC
#define testToggle_Pin GPIO_PIN_2
#define testToggle_GPIO_Port GPIOB
#define dataOut_Tx_Pin GPIO_PIN_6
#define dataOut_Tx_GPIO_Port GPIOC
#define dataOut_Rx_Pin GPIO_PIN_7
#define dataOut_Rx_GPIO_Port GPIOC
#define Tx_C2_Pin GPIO_PIN_8
#define Tx_C2_GPIO_Port GPIOC
#define Tx_C1_Pin GPIO_PIN_8
#define Tx_C1_GPIO_Port GPIOA
/* USER CODE BEGIN Private defines */

/* USER CODE END Private defines */

#ifdef __cplusplus
}
#endif

#endif /* __MAIN_H */

/************************ (C) COPYRIGHT STMicroelectronics *****END OF FILE****/

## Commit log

2019-07-16 Starting commit
    Uploading file from were I am up to this point
2019-07-20 Weekly commit 7/20/2019
    Weekly commit 7/20/2019
2019-07-25 Weekly commit 7/25/19
    Weekly commit 7/25/19
2019-08-02 Weekly Push
    Weekly Push
2019-08-09 Weekly Commit
    Weekly Commit 08/09/2019
2019-08-13 End of Rev 1.01
    End of Rev 1.01 change will be made to Rx and Bx connection in 1.02
2019-08-19 weekly commit
    weekly commit, First of Rev 1.02
2019-08-27 Weekly Commit
    Weekly Commit 8/26/2019
2019-09-19 Commit 9/19/2019
2019-10-09 backup and V2 of board
    backup and version 2 of the PCB added
2019-10-24 Add Depth Estimate to Matlab
    Add Depth Estimate to Matlab plot functions for gem data
2019-12-03 overdue backup
2020-02-04 backup
    2/04/2020
2020-02-27 Back up
    Backup of rev 2.0 for board
2020-05-07 Rev 2.0 Complete
    Rev 2.0 of PCB Completed
    SCHM, PCB layout, and gerber files generated
2021-01-11 Final Push

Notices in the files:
parts and their libraries:
Copyright 2016 Accelerated Designs. All rights reserved.
